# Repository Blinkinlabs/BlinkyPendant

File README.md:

# BlinkyPendant

The BlinkyPendant is a pocket-sized POV wand, perfect for making light effects on the go!

See [http://blinkypendant.com](http://blinkypendant.com) for more details.

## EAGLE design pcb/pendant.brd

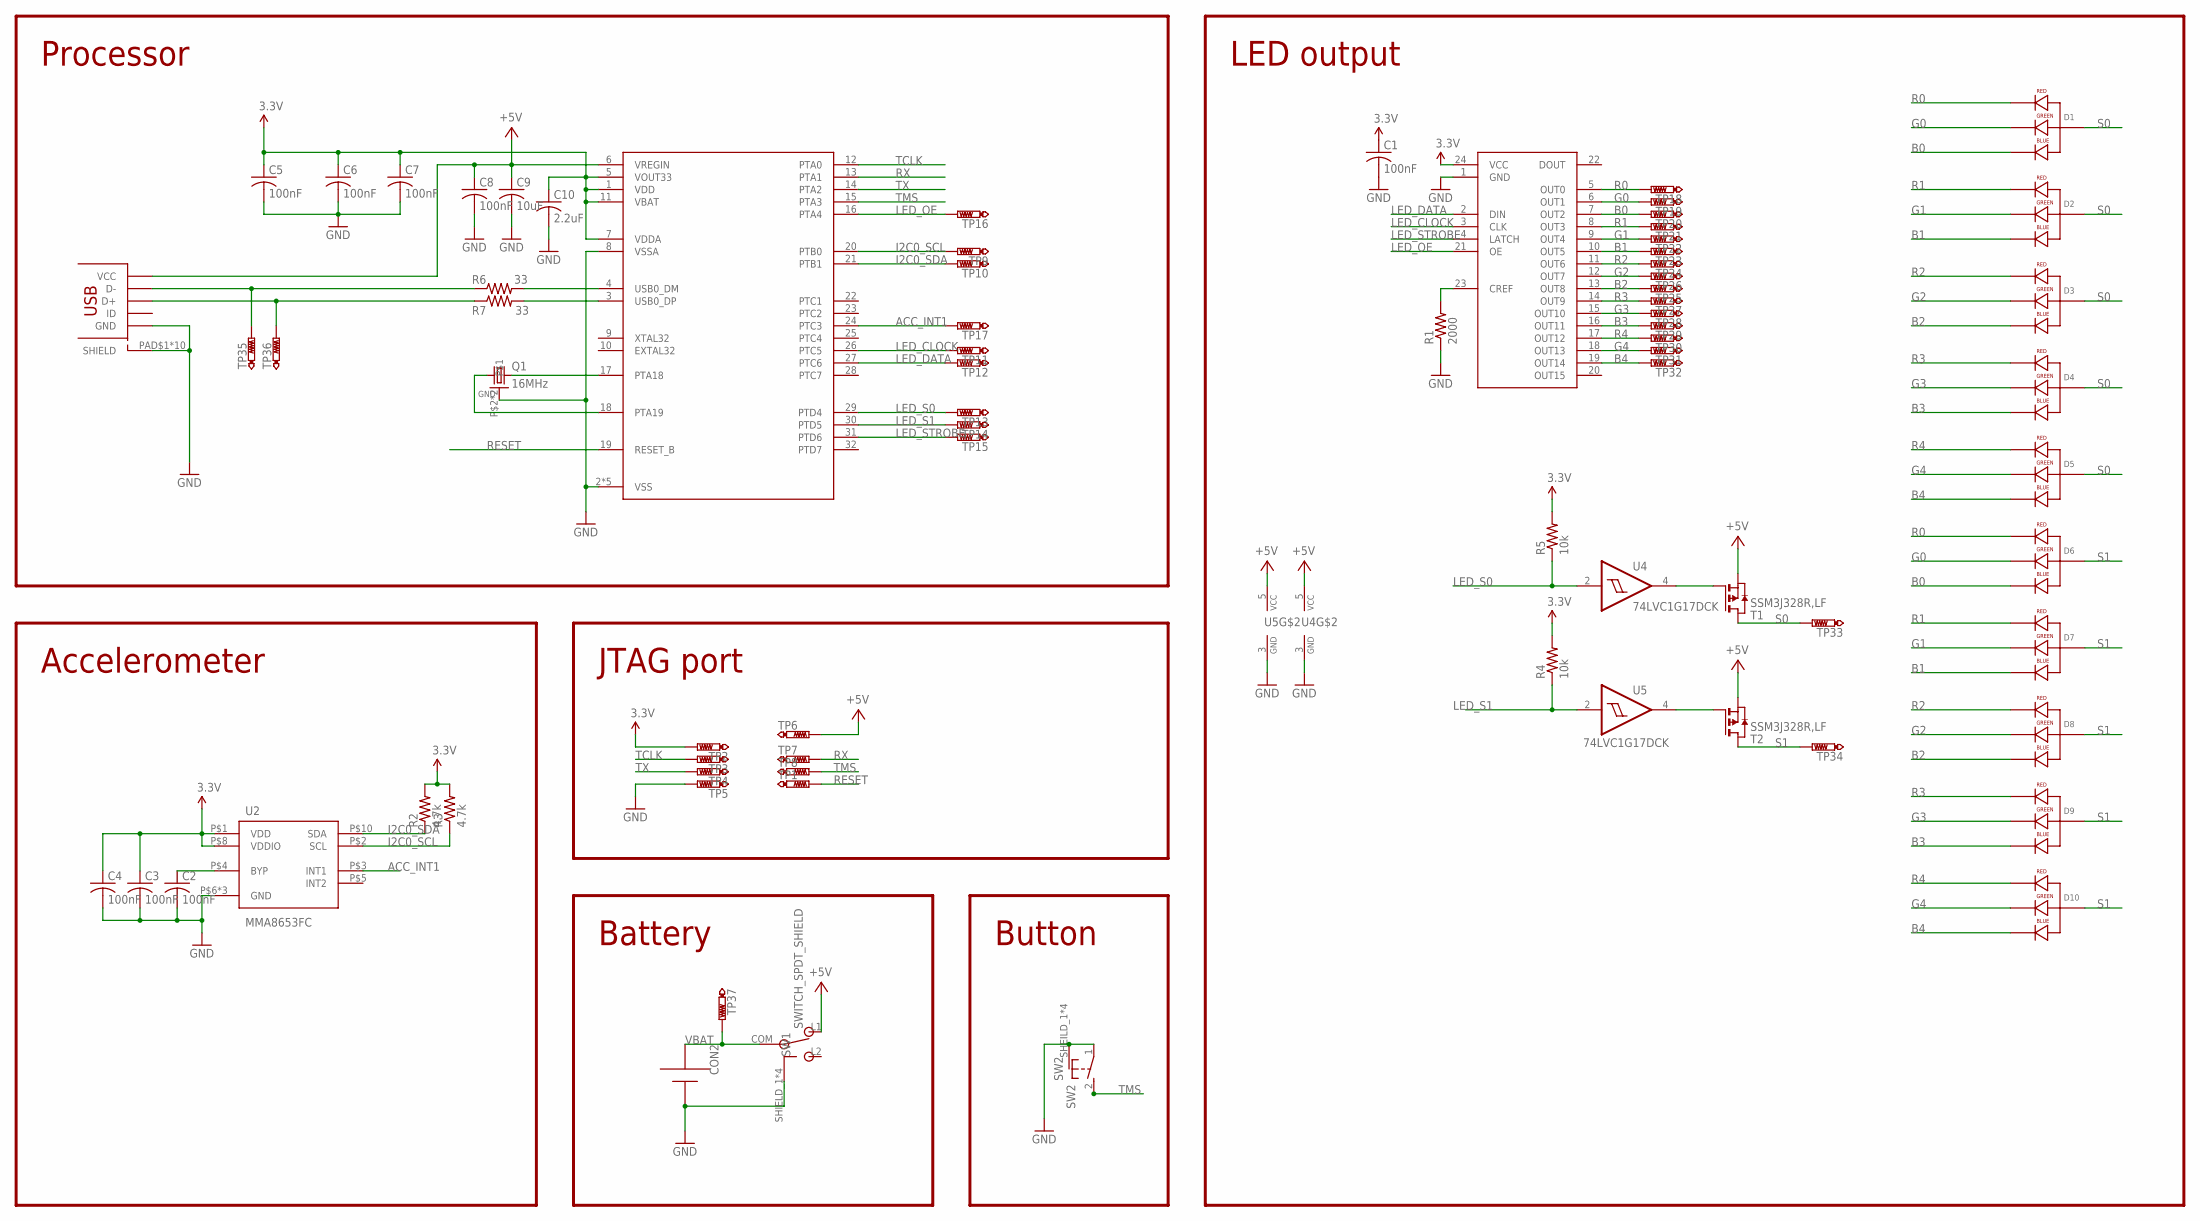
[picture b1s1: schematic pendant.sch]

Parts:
C1, C2, C3, C4, C5, C6, C7, C8: 100nF; C0402
C9: 10uF; C0603
C10: 2.2uF; C0402
CON1: USB_MICROSMT+THRUHULE; USB_MICRO_THRUHOLE
CON2: CR2032X2
D1, D2, D3, D4, D5, D6, D7, D8, D9, D10: LED-RGB5050; LED-TRICOLOR-5050-FIXED
Q1: 16MHz; CRYSTAL_3225
R1: 2000; R0402
R2, R3: 4.7k; R0402
R4, R5: 10k; R0402
R6, R7: 33; R0402
SW1: SWITCH_SPDT_SHIELD; SWITCH_SMD_90_DEGREE
SW2: SW2; BUTTON_MOMENTARY_MP5
T1, T2: SSM3J328R,LF; SOT-23
TP1, TP2, TP3, TP4, TP5, TP6, TP7, TP8, TP9, TP10, TP11, TP12, TP13, TP14, TP15, TP16, TP17, TP18, TP19, TP20, TP21, TP22, TP23, TP24, TP25, TP26, TP27, TP28, TP29, TP30, TP31, TP32, TP33, TP34, TP35, TP36, TP37: PTR1B1,27; B1,27
U1: MK20D--VFM5; QFN32_5X5_LONGLEADS
U2: MMA8653FC; VFDFN-10
U3: ICN2026DF; SMD-24-1MM
U4, U5: 74LVC1G17DCK; SC70-5

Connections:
3.3V: C1.1, C3.1, C4.1, C5.1, C6.1, C7.1, C10.1, R2.2, R3.2, R4.2, R5.2, TP2.TP, U1.1 (VDD), U1.5 (VOUT33), U1.7 (VDDA), U1.11 (VBAT), U2.P$1 (VDD), U2.P$8 (VDDIO), U3.24 (VCC)
+5V: C8.1, C9.1, CON1.PIN$1 (VCC), SW1.L1, T1.2 (S), T2.2 (S), TP6.TP, U1.6 (VREGIN), U4.5 (VCC), U5.5 (VCC)
ACC_INT1: TP17.TP, U1.24 (PTC3), U2.P$3 (INT1)
B0: D1.1 (BLUE_CATHODE), D6.1 (BLUE_CATHODE), TP20.TP, U3.7 (OUT2)
B1: D2.1 (BLUE_CATHODE), D7.1 (BLUE_CATHODE), TP23.TP, U3.10 (OUT5)
B2: D3.1 (BLUE_CATHODE), D8.1 (BLUE_CATHODE), TP25.TP, U3.13 (OUT8)
B3: D4.1 (BLUE_CATHODE), D9.1 (BLUE_CATHODE), TP29.TP, U3.16 (OUT11)
B4: D5.1 (BLUE_CATHODE), D10.1 (BLUE_CATHODE), TP32.TP, U3.19 (OUT14)
G0: D1.3 (GREEN_CATHODE), D6.3 (GREEN_CATHODE), TP19.TP, U3.6 (OUT1)
G1: D2.3 (GREEN_CATHODE), D7.3 (GREEN_CATHODE), TP22.TP, U3.9 (OUT4)
G2: D3.3 (GREEN_CATHODE), D8.3 (GREEN_CATHODE), TP26.TP, U3.12 (OUT7)
G3: D4.3 (GREEN_CATHODE), D9.3 (GREEN_CATHODE), TP28.TP, U3.15 (OUT10)
G4: D5.3 (GREEN_CATHODE), D10.3 (GREEN_CATHODE), TP31.TP, U3.18 (OUT13)
GND: C1.2, C2.2, C3.2, C4.2, C5.2, C6.2, C7.2, C8.2, C9.2, C10.2, CON1.PAD$1 (SHIELD), CON1.PAD$2 (SHIELD), CON1.PAD$3 (SHIELD), CON1.PAD$4 (SHIELD), CON1.PAD$5 (SHIELD), CON1.PAD$6 (SHIELD), CON1.PAD$7 (SHIELD), CON1.PAD$8 (SHIELD), CON1.PAD$9 (SHIELD), CON1.PAD$10 (SHIELD), CON1.PIN$5 (GND), CON2.-, Q1.P$2, Q1.P$4, R1.1, SW1.SHIELD_1 (SHIELD), SW1.SHIELD_2 (SHIELD), SW1.SHIELD_3 (SHIELD), SW1.SHIELD_4 (SHIELD), SW2.1, SW2.SHEILD_1 (SHIELD), SW2.SHEILD_2 (SHIELD), SW2.SHEILD_3 (SHIELD), SW2.SHEILD_4 (SHIELD), TP5.TP, U1.2 (VSS), U1.8 (VSSA), U1.PAD@1 (VSS), U1.PAD@4 (VSS), U1.PAD@9 (VSS), U1.PAD@11 (VSS), U2.P$6 (GND), U2.P$7 (GND), U2.P$9 (GND), U3.1 (GND), U4.3 (GND), U5.3 (GND)
I2C0_SCL: R3.1, TP9.TP, U1.20 (PTB0), U2.P$2 (SCL)
I2C0_SDA: R2.1, TP10.TP, U1.21 (PTB1), U2.P$10 (SDA)
LED_CLOCK: TP11.TP, U1.26 (PTC5), U3.3 (CLK)
LED_DATA: TP12.TP, U1.27 (PTC6), U3.2 (DIN)
LED_OE: TP16.TP, U1.16 (PTA4), U3.21 (OE)
LED_S0: R5.1, TP13.TP, U1.29 (PTD4), U4.2 (I)
LED_S1: R4.1, TP14.TP, U1.30 (PTD5), U5.2 (I)
LED_STROBE: TP15.TP, U1.31 (PTD6), U3.4 (LATCH)
unnamed: T2.3 (G), U5.4 (O)
unnamed: C2.1, U2.P$4 (BYP)
unnamed: T1.3 (G), U4.4 (O)
unnamed: Q1.P$3 (2), U1.17 (PTA18)
unnamed: Q1.P$1 (1), U1.18 (PTA19)
unnamed: CON1.PIN$3 (D+), R7.1, TP36.TP
unnamed: R6.2, U1.4 (USB0_DM)
unnamed: R7.2, U1.3 (USB0_DP)
unnamed: R1.2, U3.23 (CREF)
unnamed: CON1.PIN$2 (D-), R6.1, TP35.TP
R0: D1.2 (RED_CATHODE), D6.2 (RED_CATHODE), TP18.TP, U3.5 (OUT0)
R1: D2.2 (RED_CATHODE), D7.2 (RED_CATHODE), TP21.TP, U3.8 (OUT3)
R2: D3.2 (RED_CATHODE), D8.2 (RED_CATHODE), TP24.TP, U3.11 (OUT6)
R3: D4.2 (RED_CATHODE), D9.2 (RED_CATHODE), TP27.TP, U3.14 (OUT9)
R4: D5.2 (RED_CATHODE), D10.2 (RED_CATHODE), TP30.TP, U3.17 (OUT12)
RESET: TP1.TP, U1.19 (RESET_B)
RX: TP7.TP, U1.13 (PTA1)
S0: D1.4 (ANODE), D1.5 (ANODE), D1.6 (ANODE), D2.4 (ANODE), D2.5 (ANODE), D2.6 (ANODE), D3.4 (ANODE), D3.5 (ANODE), D3.6 (ANODE), D4.4 (ANODE), D4.5 (ANODE), D4.6 (ANODE), D5.4 (ANODE), D5.5 (ANODE), D5.6 (ANODE), T1.1 (D), TP33.TP
S1: D6.4 (ANODE), D6.5 (ANODE), D6.6 (ANODE), D7.4 (ANODE), D7.5 (ANODE), D7.6 (ANODE), D8.4 (ANODE), D8.5 (ANODE), D8.6 (ANODE), D9.4 (ANODE), D9.5 (ANODE), D9.6 (ANODE), D10.4 (ANODE), D10.5 (ANODE), D10.6 (ANODE), T2.1 (D), TP34.TP
TCLK: TP3.TP, U1.12 (PTA0)
TMS: SW2.2 (S), TP8.TP, U1.15 (PTA3)
TX: TP4.TP, U1.14 (PTA2)
VBAT: CON2.+, SW1.COM, TP37.TP

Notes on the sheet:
Accelerometer
LED output
Processor
JTAG port
Battery
Button

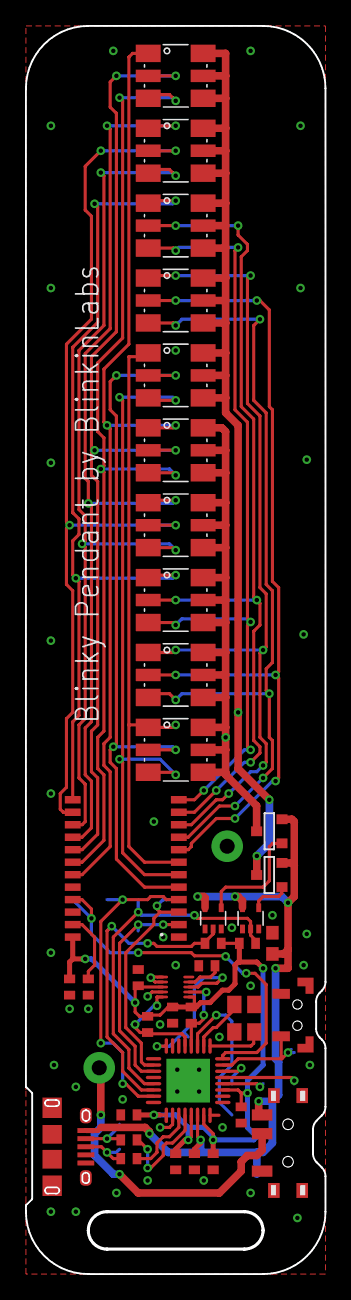
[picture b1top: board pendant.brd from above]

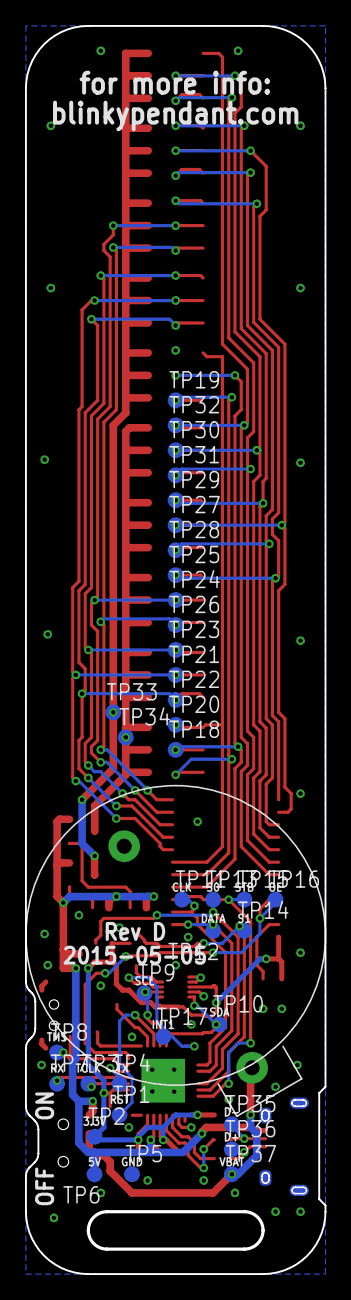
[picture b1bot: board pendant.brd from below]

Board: 2 copper layers, 23.9 x 99.9 mm, 76 parts (38 on the bottom side), 45 nets.

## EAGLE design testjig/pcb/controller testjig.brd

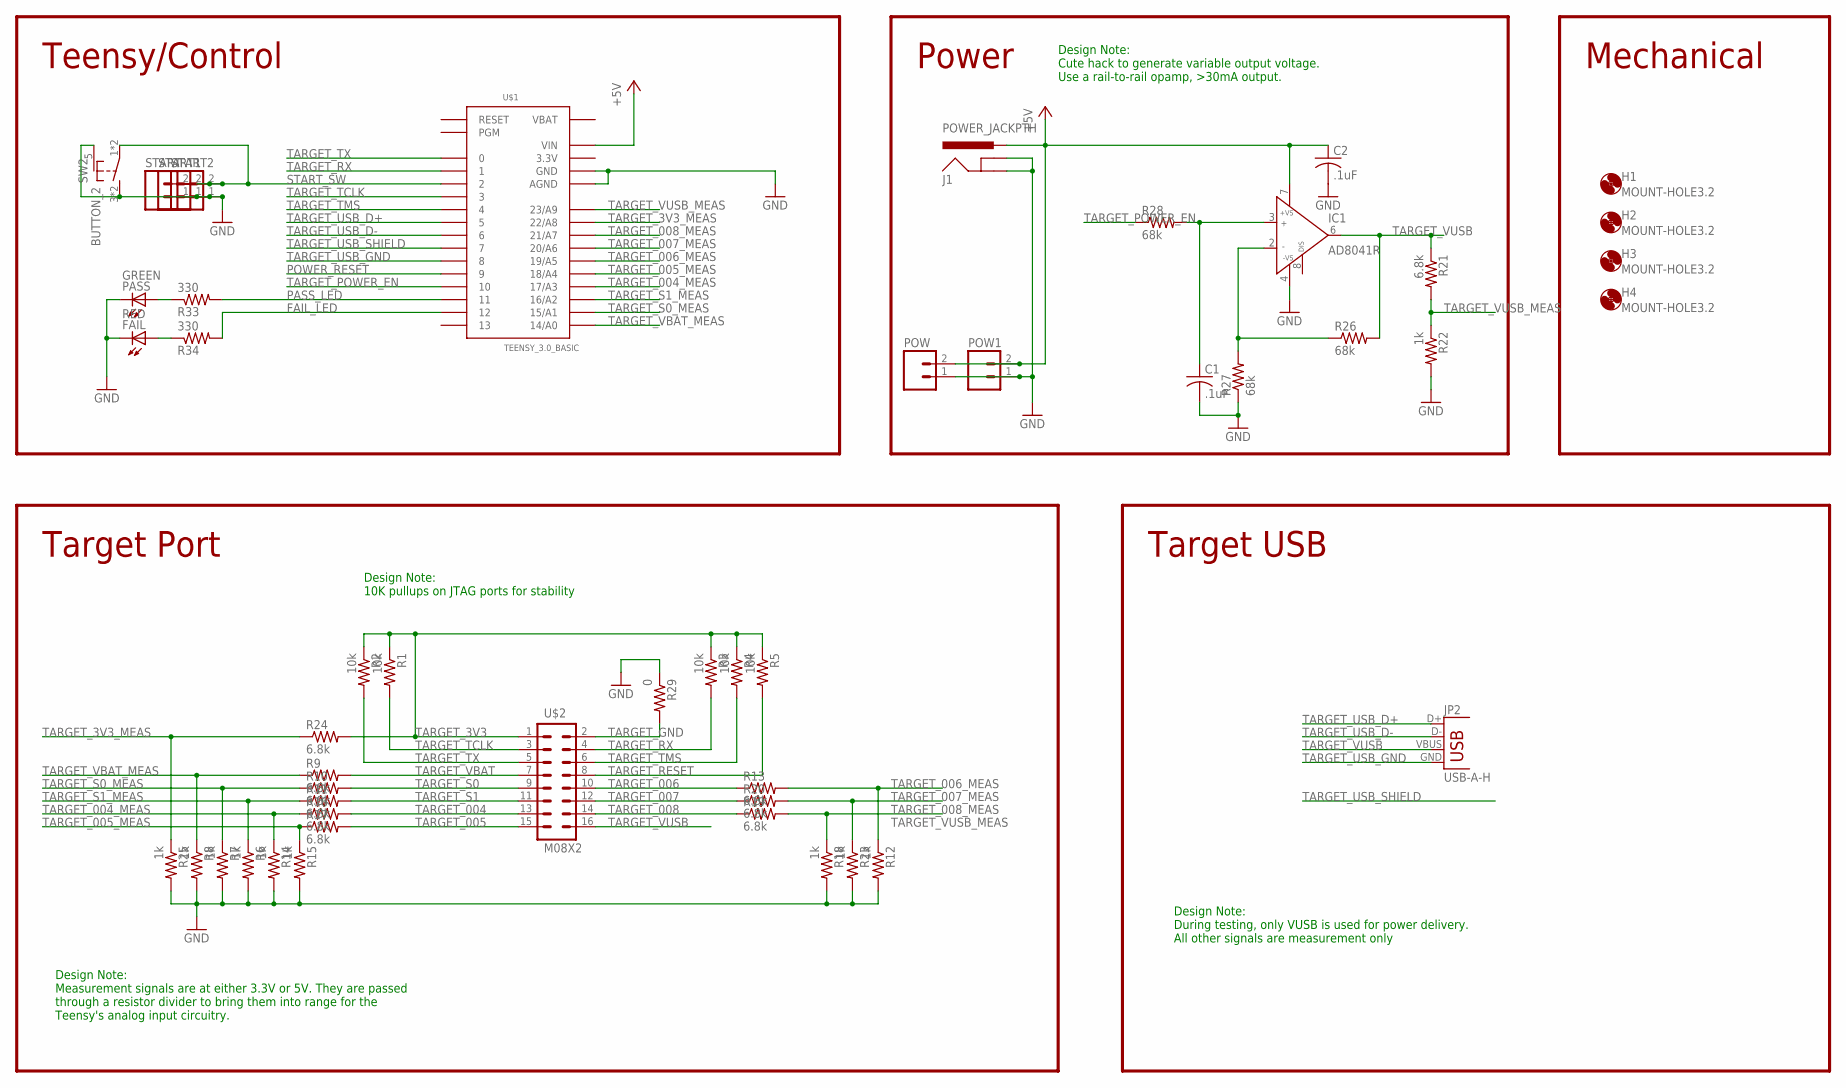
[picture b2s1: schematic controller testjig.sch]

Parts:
C1, C2: .1uF; C0603
FAIL: RED; LED5MM
H1, H2, H3, H4: MOUNT-HOLE3.2; 3,2
IC1: AD8041R; SO8
J1: POWER_JACKPTH; POWER_JACK_PTH
JP2: USB-A-H
PASS: GREEN; LED5MM
POW, POW1: M02; 02P
R1, R2, R3, R4, R5: 10k; R0603
R6, R7, R8, R12, R14, R15, R18, R22, R23, R25: 1k; R0603
R9, R10, R11, R13, R16, R17, R19, R20, R21, R24: 6.8k; R0603
R26, R27, R28: 68k; R0603
R29: 0; R0603
R33, R34: 330; R0603
START, START1, START2: M02; 02P
SW2: BUTTON_2; TD-07XB
U$1: TEENSY_3.0_BASIC
U$2: M08X2; 2X8

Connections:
3.3V: U$1.3.3V, U$1.3.3V1 (3.3V)
+5V: C2.1, IC1.7 (+VS), J1.PWR, POW.2, POW1.2, U$1.VIN
FAIL_LED: R34.2, U$1.12
GND: C1.2, C2.2, FAIL.K (C), IC1.4 (-VS), J1.GND, J1.GNDBREAK, PASS.K (C), POW.1, POW1.1, R6.2, R7.2, R8.2, R12.2, R14.2, R15.2, R18.2, R22.2, R23.2, R25.2, R27.1, R29.1, START.1, START1.1, START2.1, SW2.3 (S), SW2.4 (S), SW2.5 (SHIELD), U$1.AGND, U$1.GND, U$1.GND1 (GND)
GOOD: PASS.A, R33.1
unnamed: IC1.2 (IN-), R26.1, R27.2
unnamed: C1.1, IC1.3 (IN+), R28.2
unnamed: FAIL.A, R34.1
PASS_LED: R33.2, U$1.11
POWER_RESET: U$1.9
START_SW: START.2, START1.2, START2.2, SW2.1, SW2.2, U$1.2
TARGET_3V3: R1.1, R2.1, R3.1, R4.1, R5.1, R24.2, U$2.1
TARGET_3V3_MEAS: R24.1, R25.1, U$1.22/A8
TARGET_004: R16.2, U$2.13
TARGET_004_MEAS: R14.1, R16.1, U$1.17/A3
TARGET_005: R17.2, U$2.15
TARGET_005_MEAS: R15.1, R17.1, U$1.18/A4
TARGET_006: R13.1, U$2.10
TARGET_006_MEAS: R12.1, R13.2, U$1.19/A5
TARGET_007: R20.1, U$2.12
TARGET_007_MEAS: R20.2, R23.1, U$1.20/A6
TARGET_008: R19.1, U$2.14
TARGET_008_MEAS: R18.1, R19.2, U$1.21/A7
TARGET_GND: R29.2, U$2.2
TARGET_POWER_EN: R28.1, U$1.10
TARGET_RESET: R5.2, U$2.8
TARGET_RX: R3.2, U$1.1, U$2.4
TARGET_S0: R10.2, U$2.9
TARGET_S0_MEAS: R7.1, R10.1, U$1.15/A1
TARGET_S1: R11.2, U$2.11
TARGET_S1_MEAS: R6.1, R11.1, U$1.16/A2
TARGET_TCLK: R1.2, U$1.3, U$2.3
TARGET_TMS: R4.2, U$1.4, U$2.6
TARGET_TX: R2.2, U$1.0, U$2.5
TARGET_USB_D+: JP2.D+, U$1.5
TARGET_USB_D-: JP2.D-, U$1.6
TARGET_USB_GND: JP2.GND, U$1.8
TARGET_USB_SHIELD: U$1.7
TARGET_VBAT: R9.2, U$2.7
TARGET_VBAT_MEAS: R8.1, R9.1, U$1.14/A0
TARGET_VUSB: IC1.6 (OUT), JP2.VBUS, R21.1, R26.2, U$2.16
TARGET_VUSB_MEAS: R21.2, R22.1, U$1.23/A9
VBAT: U$1.VBAT

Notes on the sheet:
Teensy/Control
Target Port
Design Note: Measurement signals are at either 3.3V or 5V. They are passed through a resistor divider to bring them into range for the Teensy's analog input circuitry.
Design Note: 10K pullups on JTAG ports for stability
Mechanical
Target USB
Power
Design Note: During testing, only VUSB is used for power delivery. All other signals are measurement only
Design Note: Cute hack to generate variable output voltage. Use a rail-to-rail opamp, >30mA output.

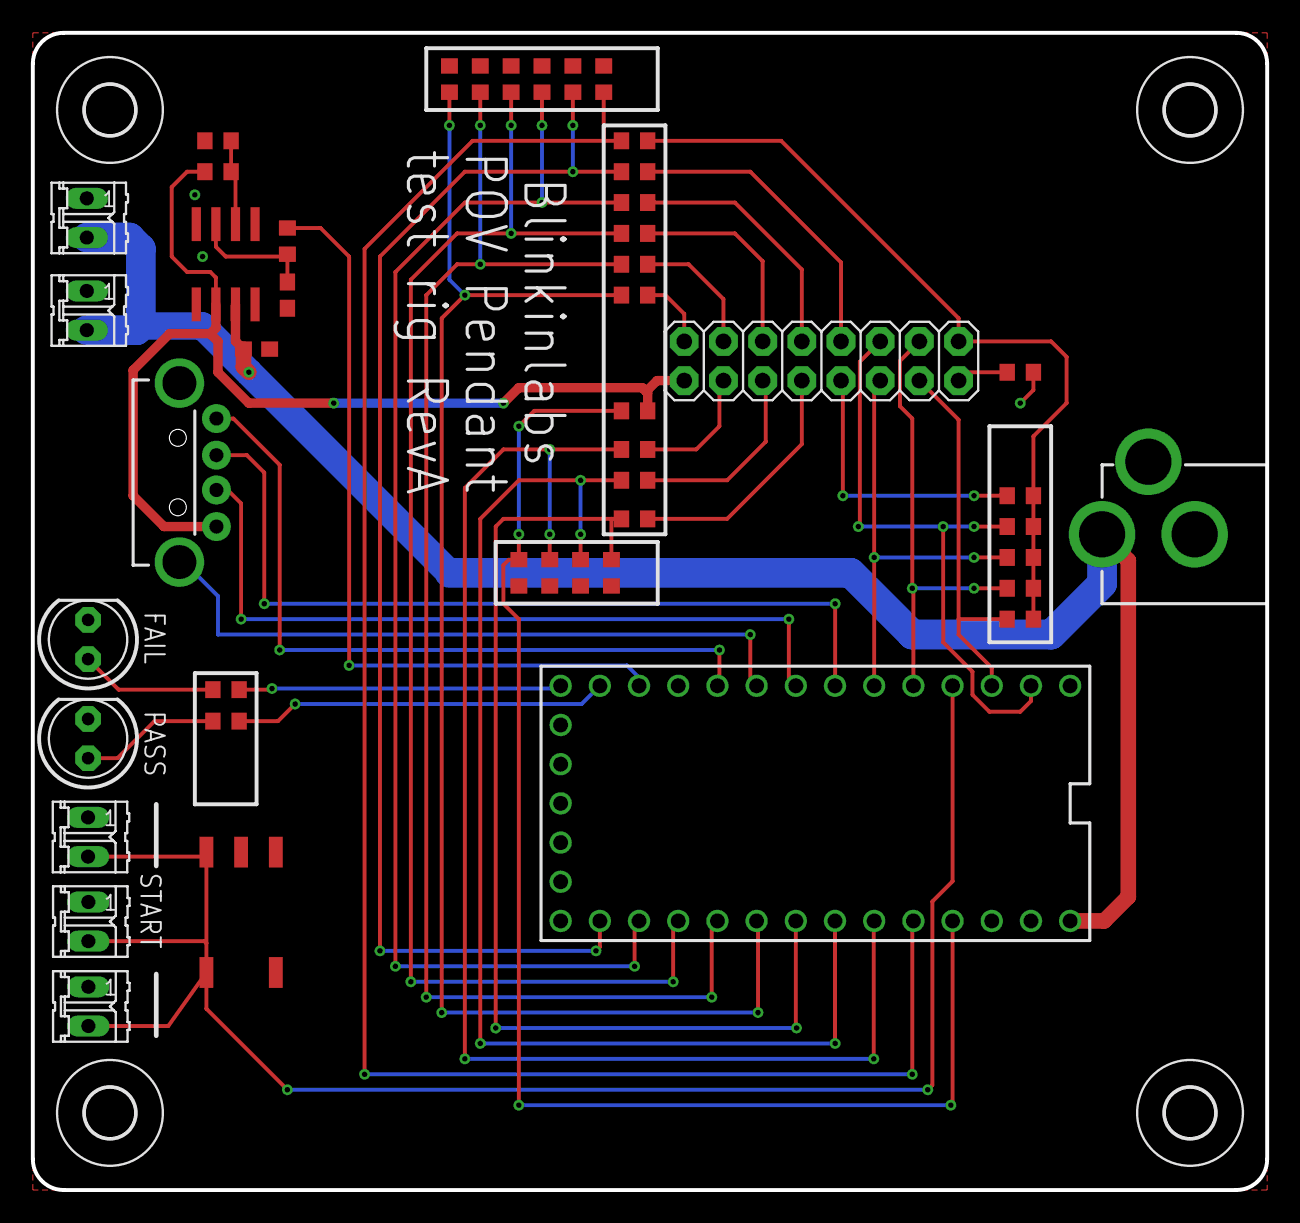
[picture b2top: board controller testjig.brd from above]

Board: 2 copper layers, 80.0 x 75.0 mm, 50 parts (0 on the bottom side), 40 nets.

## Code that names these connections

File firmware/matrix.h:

/*
 * DMA Matrix Driver
 * 
 * Copyright (c) 2014 Matt Mets
 * 
 * Permission is hereby granted, free of charge, to any person obtaining a copy of
 * this software and associated documentation files (the "Software"), to deal in
 * the Software without restriction, including without limitation the rights to
 * use, copy, modify, merge, publish, distribute, sublicense, and/or sell copies of
 * the Software, and to permit persons to whom the Software is furnished to do so,
 * subject to the following conditions:
 * 
 * The above copyright notice and this permission notice shall be included in all
 * copies or substantial portions of the Software.
 * 
 * THE SOFTWARE IS PROVIDED "AS IS", WITHOUT WARRANTY OF ANY KIND, EXPRESS OR
 * IMPLIED, INCLUDING BUT NOT LIMITED TO THE WARRANTIES OF MERCHANTABILITY, FITNESS
 * FOR A PARTICULAR PURPOSE AND NONINFRINGEMENT. IN NO EVENT SHALL THE AUTHORS OR
 * COPYRIGHT HOLDERS BE LIABLE FOR ANY CLAIM, DAMAGES OR OTHER LIABILITY, WHETHER
 * IN AN ACTION OF CONTRACT, TORT OR OTHERWISE, ARISING FROM, OUT OF OR IN
 * CONNECTION WITH THE SOFTWARE OR THE USE OR OTHER DEALINGS IN THE SOFTWARE.
 */

#ifndef MATRIX_H
#define MATRIX_H

#include "WProgram.h"
#include "pins_arduino.h"
#include "blinkypendant.h"

//Display Geometry
#define BIT_DEPTH 8       // Color bits per channel (Note: input is always 8 bit)

// Output assignments
// Note: These can't be changed arbitrarily- the GPIOs are actually
// referred to in the library by their port assignments.
#define LED_DATA_PIN  12   // Port C, output 6
#define LED_CLOCK_PIN  11   // Port C, output 5
#define LED_STROBE_PIN  16   // Port D, output 6
#define LED_OE_PIN    4   // FTM0 channel 1 / Port A, output 4
#define S0       14   // Port D, output 4
#define S1       15   // Port D, output 5

// RGB pixel type
struct Pixel {
  uint8_t R;
  uint8_t G;
  uint8_t B;
};

// Set up the matrix and start running it's display loop
extern void matrixSetup();

// Re-start a paused matrix
extern void matrixStart();

// Change the system brightness
// @param brightness Display brightness scale, from 0 (off) to 1 (fully on)
extern void setBrightness(float brightness);

// Update a single pixel in the array
// @param column int Pixel column (0 to LED_COLS - 1)
// @param row int Pixel row (0 to LED_ROWS - 1)
// @param value uint8_t New value for the pixel (0 - 255)
extern void setPixel(int column, int row, uint8_t r, uint8_t g, uint8_t b);

// Update the matrix using the data in the Pixels[] array
extern void show();

// Get the display pixel buffer
// @return Pointer to the pixel display buffer, a uint8_t array of size
// LED_ROWS*LED_COLS
// TODO: Change to pixel type...
extern Pixel* getPixels();

// The display is double-buffered internally. This function returns
// true if there is already an update waiting.
extern bool bufferWaiting();

#endif

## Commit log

2015-04-08 First commit, pull firmware from leoblinky, bootloader from blinkytile, new pcb design
2015-04-08 Working toward a stable bootloader
2015-04-08 Pull firmware from BlinkyTile controller instead, so we can integrate matrix into it.
2015-04-08 Get things compiled, output not working yet
2015-04-08 Almost there! Need to flip OE to timer 0.
2015-04-08 Add matrix functions
2015-04-11 fix cap under ICN2026, change led output order, use 5050 LEDs, replace power and tach switches, use 10 LEDs, move test points out from battery
2015-04-12 Update battery footprint
2015-04-12 Display going, some bleeding and bit order is wrong.
2015-04-12 Closer
2015-04-12 Working
2015-04-12 adding animations
2015-04-12 Adding support for accelerometer
2015-04-12 Accelerometer working with cheap 1 point derivative filter.
2015-04-13 Add interrupt line from accelerometer, clean up test pad positions
2015-04-15 Update I2C speed
2015-04-17 Jerk-based scrubbing
2015-04-17 Switching to class-based implementation
2015-04-18 Tweakig POV code
2015-04-19 Support switching between animations
2015-04-19 Rename the POV files
2015-04-19 Closer and closer
2015-04-19 Even closer!
2015-04-20 Closing in on RevC design
2015-04-21 RevC PCB
2015-04-21 POV: Use a timer to count time, rather than rely on millis()
2015-04-30 Add test jig RevA
2015-05-05 Update board
2015-05-05 Add USB, VBAT test points
2015-05-05 RevD!!!
2015-05-05 Add artwork files
2015-05-06 Update reference designators
2015-05-08 Fix VBAT label (minor point)
2015-05-19 Add Apache license
2015-05-20 Update reference designators on the BOM
2015-05-24 Update VID/PID
2015-05-24 Stable testing version of firmware for test jig
2015-05-24 Add some more sample images
2015-05-24 Binaries for newer application images
2015-05-24 Update application name
2015-05-26 Bringing up the test rig
2015-05-26 Reliable reset sequence
2015-05-26 Add S0, S1 tests, begin I2C work for accelerometer
2015-05-26 Broken accelerometer testing
2015-05-27 Fix target poweroff routine, add nonworking LED test
2015-05-27 Working at high speed on Teensy 3.0. Problem was in the reset sequence.
2015-05-27 Fix bug in i2c register defines
2015-05-27 Add timeouts to I2C driver, so it can fail gracelfully
2015-05-27 Accelerometer test
2015-05-27 Accelerometer works, add white LED flashing
2015-05-28 Update makefile to use new VID
2015-05-28 Remove some unused files
2015-05-28 Reduce animation memory usage
2015-05-28 Remove some more unused code, build new test rig image
2015-05-28 Bring back the flexram-based bootloader since we have flexram in this applicaiton.
2015-05-28 Almost working image loader
2015-05-28 Revert use of flexram in bootloader
2015-05-28 Remove unused linker define
2015-05-28 Pushing on with flexram based animation loader for the moment
2015-05-28 Add python example for talking to the pendant
2015-05-28 Unknown
2015-05-28 Slow down color tests a bit
2015-05-28 Update bootloader with new name
2015-05-28 Enable blinkytape protocol on the serial port
2015-05-28 Simple write-to-flash achieved
2015-05-28 Default animations coexist with user animation
2015-05-28 Add beginning of a read function
2015-05-29 Add more animations, first pass at detection of the saved animation
2015-05-29 Mostly working?
2015-05-29 Production fix: can't use flexram for programming since it's not present
2015-05-29 Production speedup: avoid redundant transactions when programming flash
2015-05-29 Production images!
2015-05-30 Generate Windows drivers for the pendant
2015-05-30 Bugfix for DFU runtime VID
2015-05-30 Fix in listports to work with windows
2015-07-19 Support multiple patterns from the flash!
2015-07-19 Update core pins to match the processor
2015-07-19 Fix for compiler warning
2015-11-23 Bugfix: Report new firmware version to differentiate new features
2016-10-25 Add travis ci file
2016-10-25 Fix caps error
2017-05-10 Remove conflicting math function
2017-05-10 Remove outdated examples
2017-05-10 Fix pattern loading bug
2017-05-10 Update readme to point to new toolchain
2017-05-10 Remove old code
2017-05-10 Put flash animation functions into seperate directory
2017-05-10 Bump version, replace LED_COUNT with DISPLAY_MODE
2017-05-10 Fix references to blinkytile
2017-05-10 First pass at a timed mode
2017-05-11 Improve performance in serial loop mode
2017-05-11 Bugfix: call matrixSetup() after write
2017-05-11 Add v300 firmware
2017-05-11 Remove old firmware images
2017-05-11 Remove more old images
2017-05-11 Add 2.0.0 firmware
2017-10-18 Add license, simple readme
2017-10-18 Add link to project page
2017-10-18 Move test code to production directory
2017-10-18 Fix v200 firmware: it was somehow overwritten by lightbuddy fw

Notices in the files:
parts and their libraries:
SparkFun-Aesthetics: Licensing: CC v3.0 Share-Alike You are welcome to use this library for commercial purposes.
